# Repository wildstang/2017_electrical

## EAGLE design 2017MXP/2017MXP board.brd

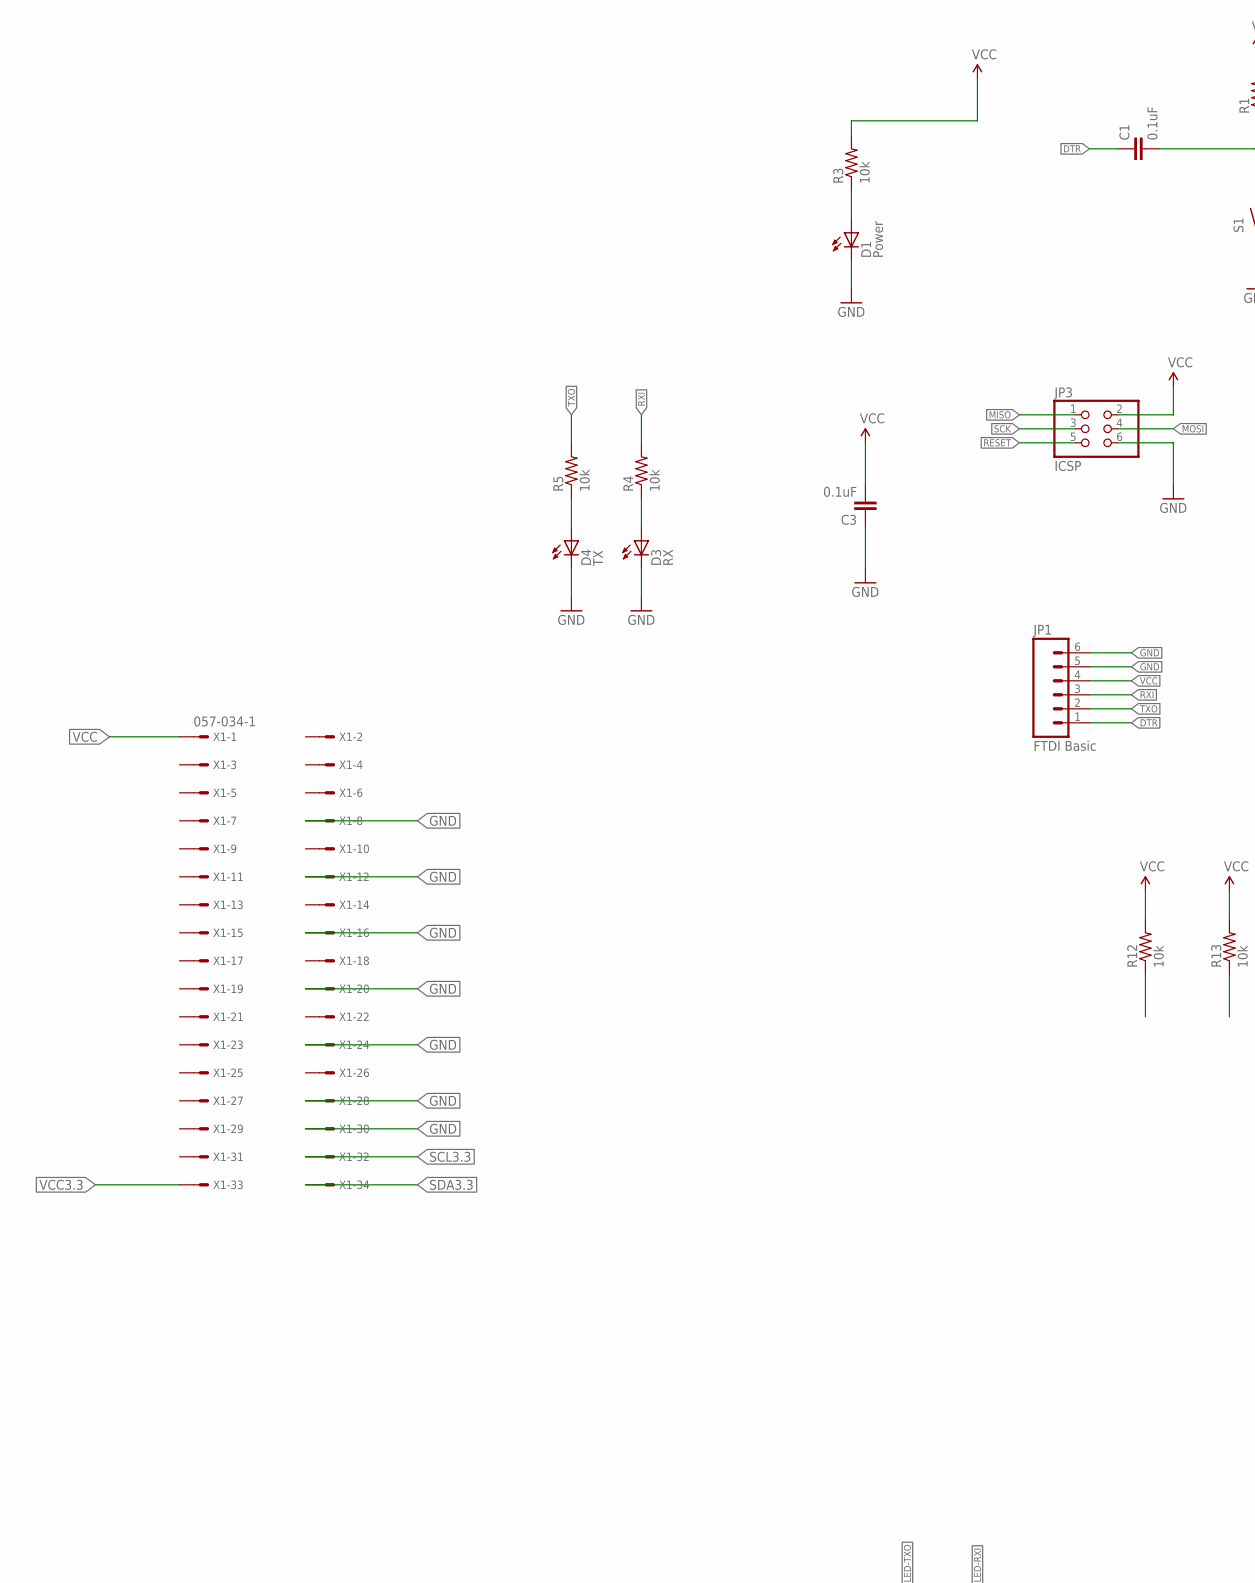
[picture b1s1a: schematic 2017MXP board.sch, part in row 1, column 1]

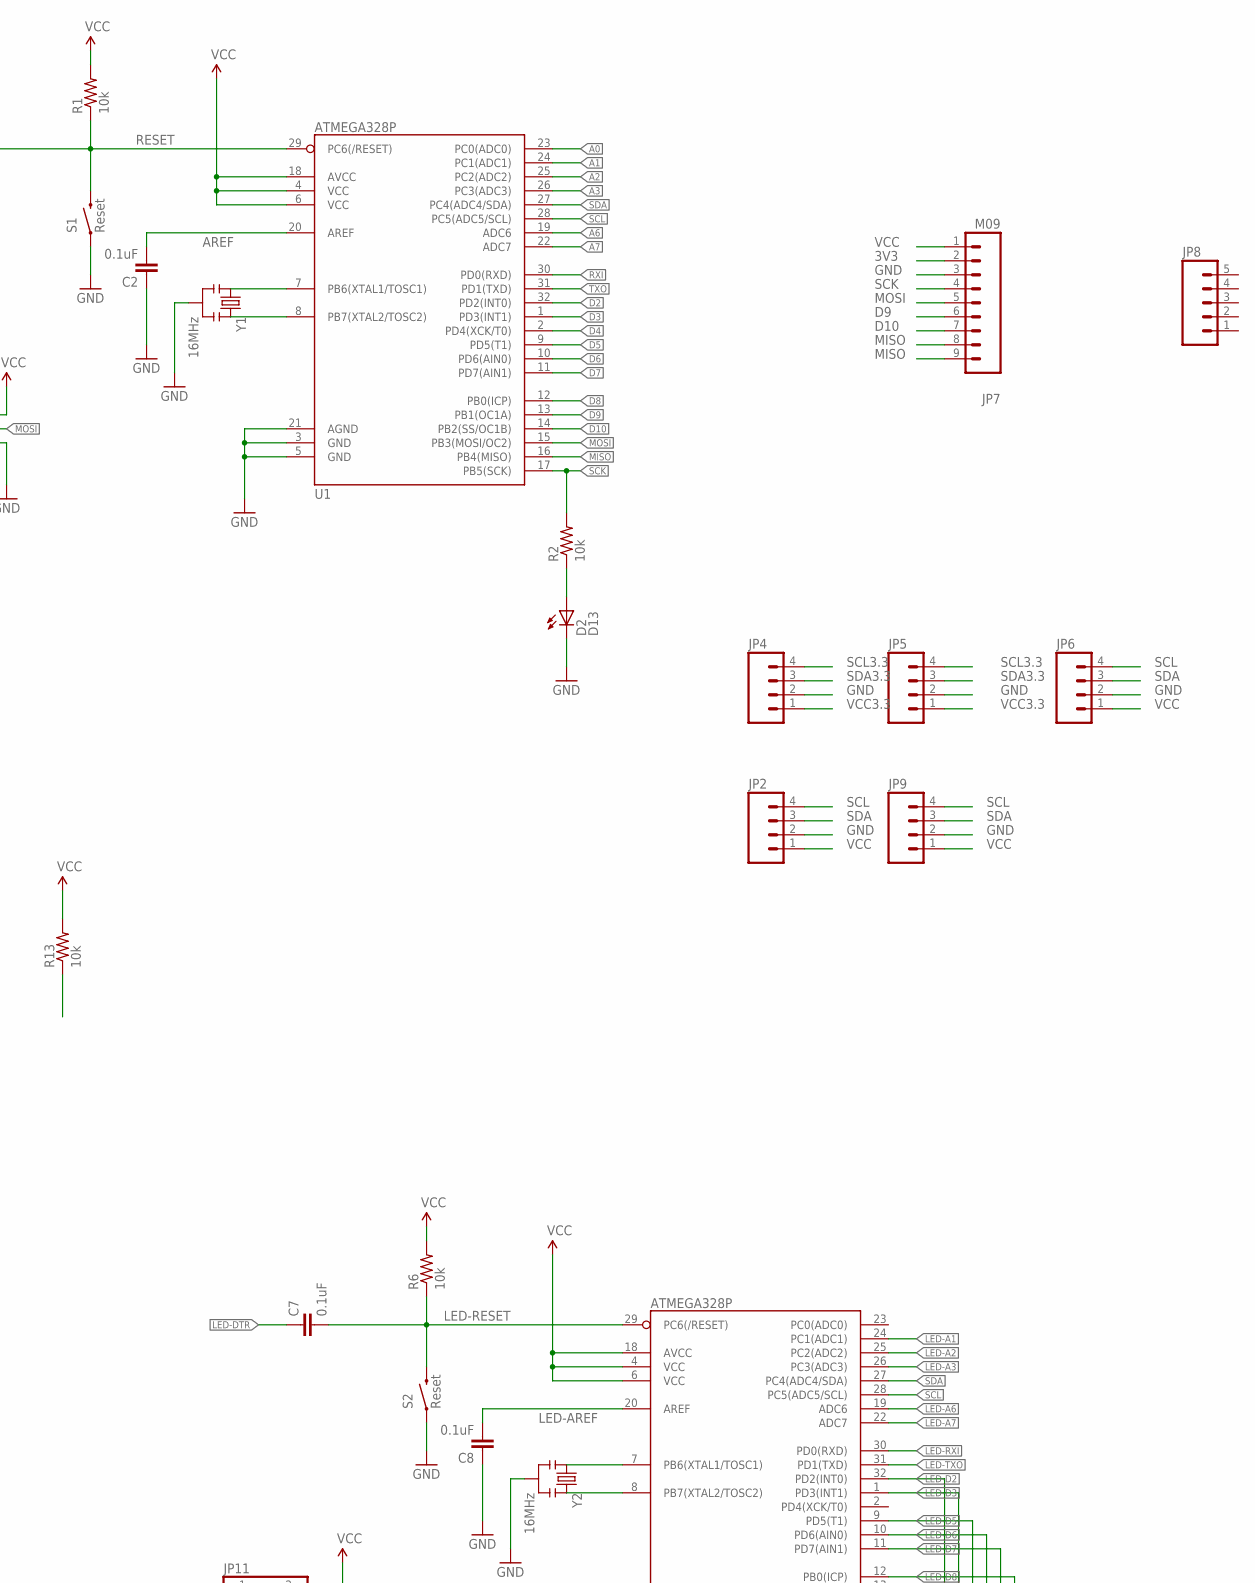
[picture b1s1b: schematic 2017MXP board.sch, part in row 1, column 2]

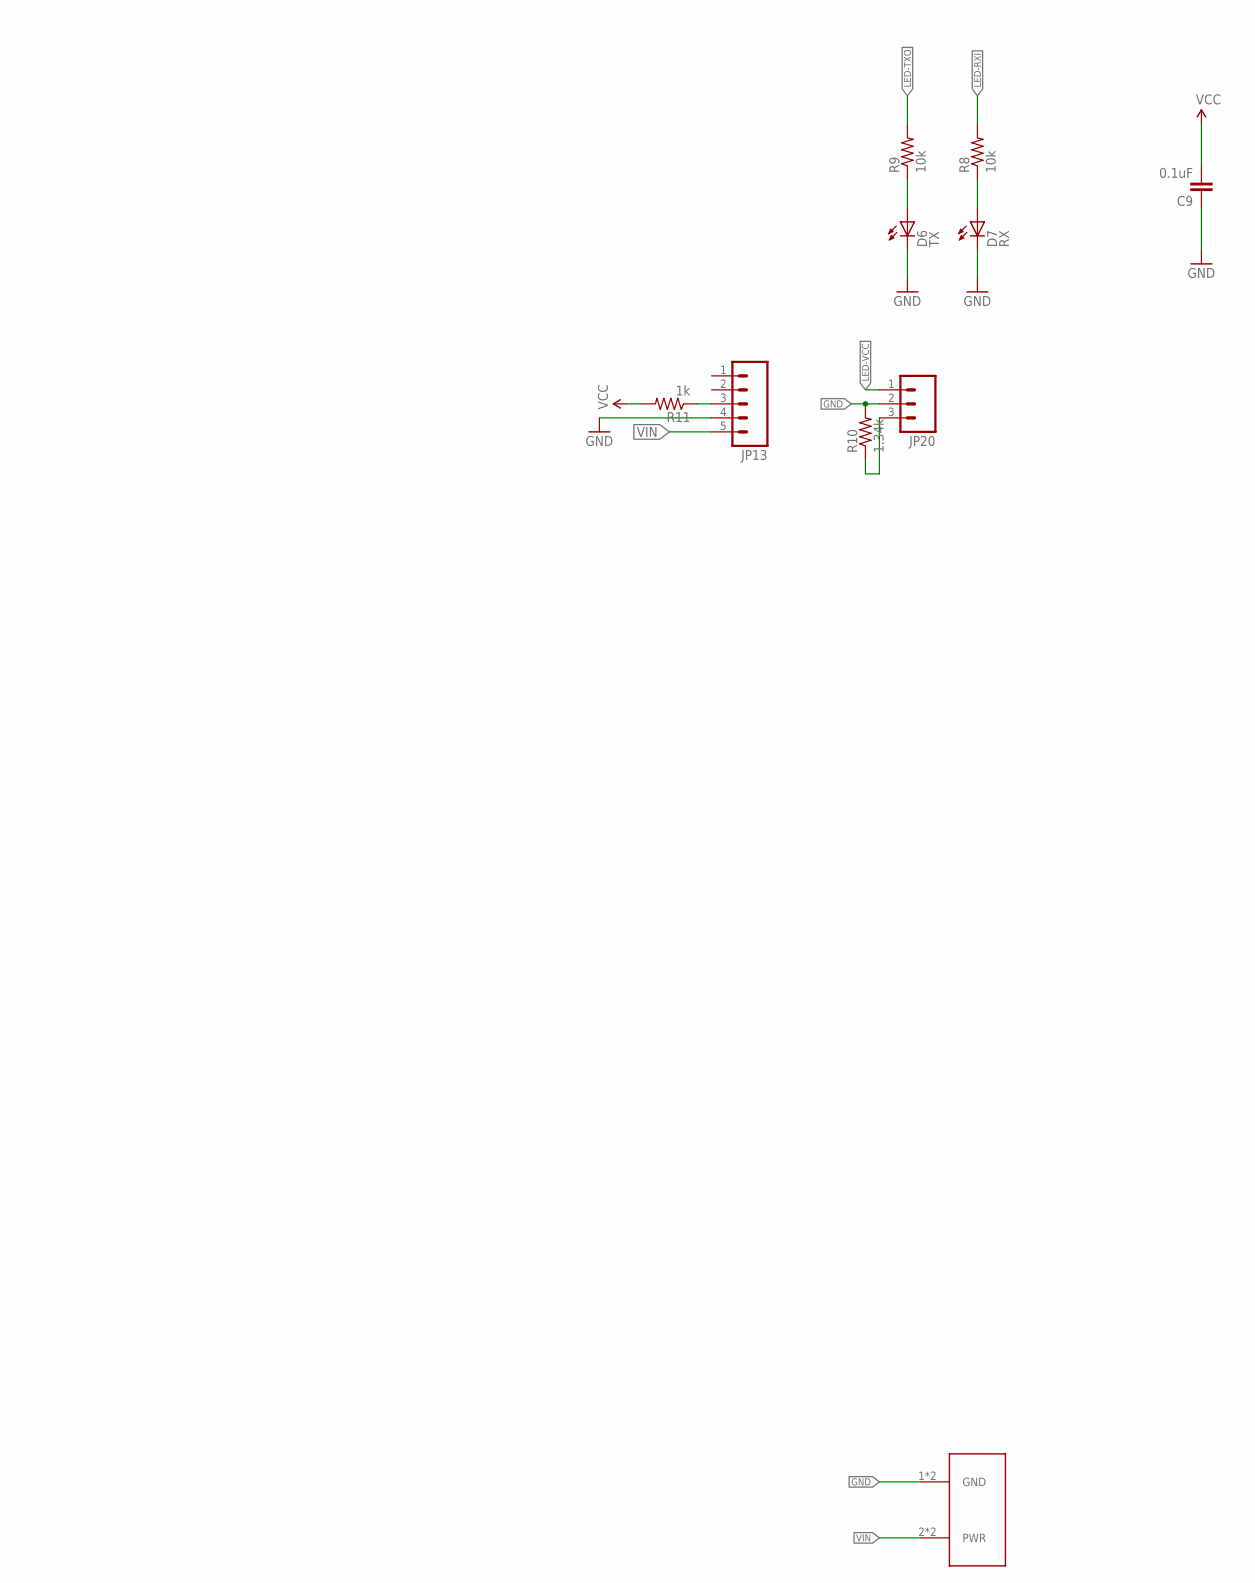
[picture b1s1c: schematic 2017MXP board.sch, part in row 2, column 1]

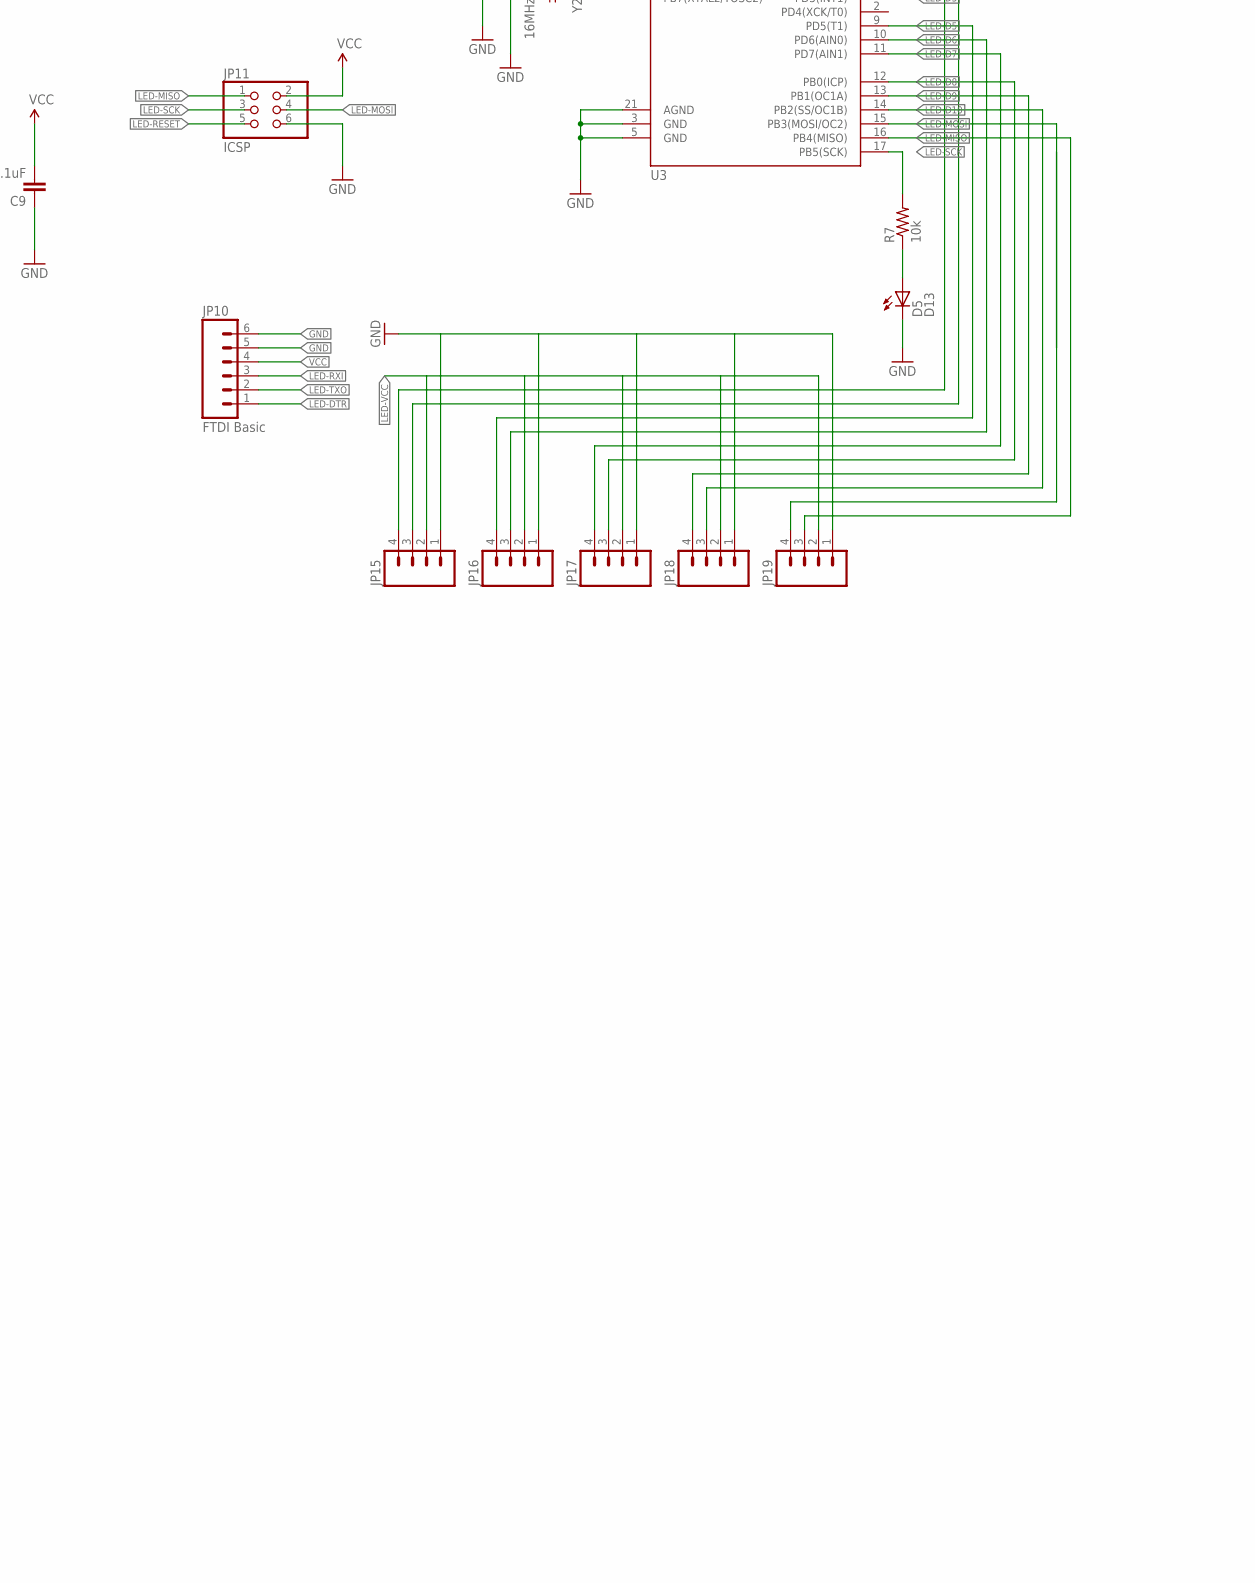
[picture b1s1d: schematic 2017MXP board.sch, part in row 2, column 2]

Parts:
C1, C2, C3, C7, C8, C9: 0.1uF; 0603-CAP
D1: Power; LED-0603
D2, D5: D13; LED-0603
D3, D7: RX; LED-0603
D4, D6: TX; LED-0603
JP1, JP10: FTDI Basic; 1X06
JP2, JP4, JP5, JP6, JP9, JP15, JP16, JP17, JP18, JP19: M04PTH; 1X04
JP3, JP11: ICSP; 2X03
JP7: M09; 1X09
JP8, JP13: M05PTH; 1X05
JP20: M03PTH; 1X03
R1, R2, R3, R4, R5, R6, R7, R8, R9, R12, R13: 10k; 0603-RES
R10: 1.34k; AXIAL-0.3
R11: 1k; AXIAL-0.3
S1, S2: Reset; TACTILE_SWITCH_SMD
U1, U3: ATMEGA328P; TQFP32-08
U$2: LSF-SMT
X1: 057-034-1
Y1, Y2: 16MHz; RESONATOR-SMD

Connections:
3V3: JP7.2
A0: U1.23 (PC0(ADC0))
A1: U1.24 (PC1(ADC1))
A2: U1.25 (PC2(ADC2))
A3: U1.26 (PC3(ADC3))
A6: U1.19 (ADC6)
A7: U1.22 (ADC7)
AREF: C2.2, U1.20 (AREF)
D2: U1.32 (PD2(INT0))
D3: U1.1 (PD3(INT1))
D4: U1.2 (PD4(XCK/T0))
D5: U1.9 (PD5(T1))
D6: U1.10 (PD6(AIN0))
D7: U1.11 (PD7(AIN1))
D8: U1.12 (PB0(ICP))
D9: JP7.6, U1.13 (PB1(OC1A))
D10: JP7.7, U1.14 (PB2(SS/OC1B))
DTR: C1.1, JP1.1
GND: C2.1, C3.1, C8.1, C9.1, D1.C, D2.C, D3.C, D4.C, D5.C, D6.C, D7.C, JP1.5, JP1.6, JP2.2, JP3.6, JP4.2, JP5.2, JP6.2, JP7.3, JP9.2, JP10.5, JP10.6, JP11.6, JP13.4, JP15.1, JP16.1, JP17.1, JP18.1, JP19.1, JP20.2, R10.P$2 (2), S1.1, S2.1, U1.3 (GND), U1.5 (GND), U1.21 (AGND), U3.3 (GND), U3.5 (GND), U3.21 (AGND), U$2.1 (GND), U$2.1-2 (GND), X1.8, X1.12, X1.16, X1.20, X1.24, X1.28, X1.30, Y1.2, Y2.2
LED-A1: U3.24 (PC1(ADC1))
LED-A2: U3.25 (PC2(ADC2))
LED-A3: U3.26 (PC3(ADC3))
LED-A6: U3.19 (ADC6)
LED-A7: U3.22 (ADC7)
LED-AREF: C8.2, U3.20 (AREF)
LED-D2: JP15.4, U3.32 (PD2(INT0))
LED-D3: JP15.3, U3.1 (PD3(INT1))
LED-D5: JP16.4, U3.9 (PD5(T1))
LED-D6: JP16.3, U3.10 (PD6(AIN0))
LED-D7: JP17.4, U3.11 (PD7(AIN1))
LED-D8: JP17.3, U3.12 (PB0(ICP))
LED-D9: JP18.4, U3.13 (PB1(OC1A))
LED-D10: JP18.3, U3.14 (PB2(SS/OC1B))
LED-DTR: C7.1, JP10.1
LED-MISO: JP11.1, JP19.3, U3.16 (PB4(MISO))
LED-MOSI: JP11.4, JP19.4, U3.15 (PB3(MOSI/OC2))
LED-RESET: C7.2, JP11.5, R6.1, S2.3 (2), U3.29 (PC6(/RESET))
LED-RXI: JP10.3, R8.2, U3.30 (PD0(RXD))
LED-SCK: JP11.3, R7.2, U3.17 (PB5(SCK))
LED-TXO: JP10.2, R9.2, U3.31 (PD1(TXD))
LED-VCC: JP15.2, JP16.2, JP17.2, JP18.2, JP19.2, JP20.1
MISO: JP3.1, JP7.8, JP7.9, U1.16 (PB4(MISO))
MOSI: JP3.4, JP7.5, U1.15 (PB3(MOSI/OC2))
unnamed: U1.7 (PB6(XTAL1/TOSC1)), Y1.1
unnamed: U1.8 (PB7(XTAL2/TOSC2)), Y1.3
unnamed: D1.A, R3.1
unnamed: D2.A, R2.1
unnamed: D3.A, R4.1
unnamed: D4.A, R5.1
unnamed: U3.7 (PB6(XTAL1/TOSC1)), Y2.1
unnamed: U3.8 (PB7(XTAL2/TOSC2)), Y2.3
unnamed: D5.A, R7.1
unnamed: D6.A, R9.1
unnamed: D7.A, R8.1
unnamed: JP20.3, R10.P$1 (1)
unnamed: JP13.3, R11.P$1 (1)
RESET: C1.2, JP3.5, R1.1, S1.3 (2), U1.29 (PC6(/RESET))
RXI: JP1.3, R4.2, U1.30 (PD0(RXD))
SCK: JP3.3, JP7.4, R2.2, U1.17 (PB5(SCK))
SCL: JP2.4, JP6.4, JP9.4, R13.1, U1.28 (PC5(ADC5/SCL)), U3.28 (PC5(ADC5/SCL))
SCL3.3: JP4.4, JP5.4, X1.32
SDA: JP2.3, JP6.3, JP9.3, R12.1, U1.27 (PC4(ADC4/SDA)), U3.27 (PC4(ADC4/SDA))
SDA3.3: JP4.3, JP5.3, X1.34
TXO: JP1.2, R5.2, U1.31 (PD1(TXD))
VCC: C3.2, C9.2, JP1.4, JP2.1, JP3.2, JP6.1, JP7.1, JP9.1, JP10.4, JP11.2, R1.2, R3.2, R6.2, R11.P$2 (2), R12.2, R13.2, U1.4 (VCC), U1.6 (VCC), U1.18 (AVCC), U3.4 (VCC), U3.6 (VCC), U3.18 (AVCC), X1.1
VCC3.3: JP4.1, JP5.1, X1.33
VIN: JP13.5, U$2.2 (PWR), U$2.2-2 (PWR)

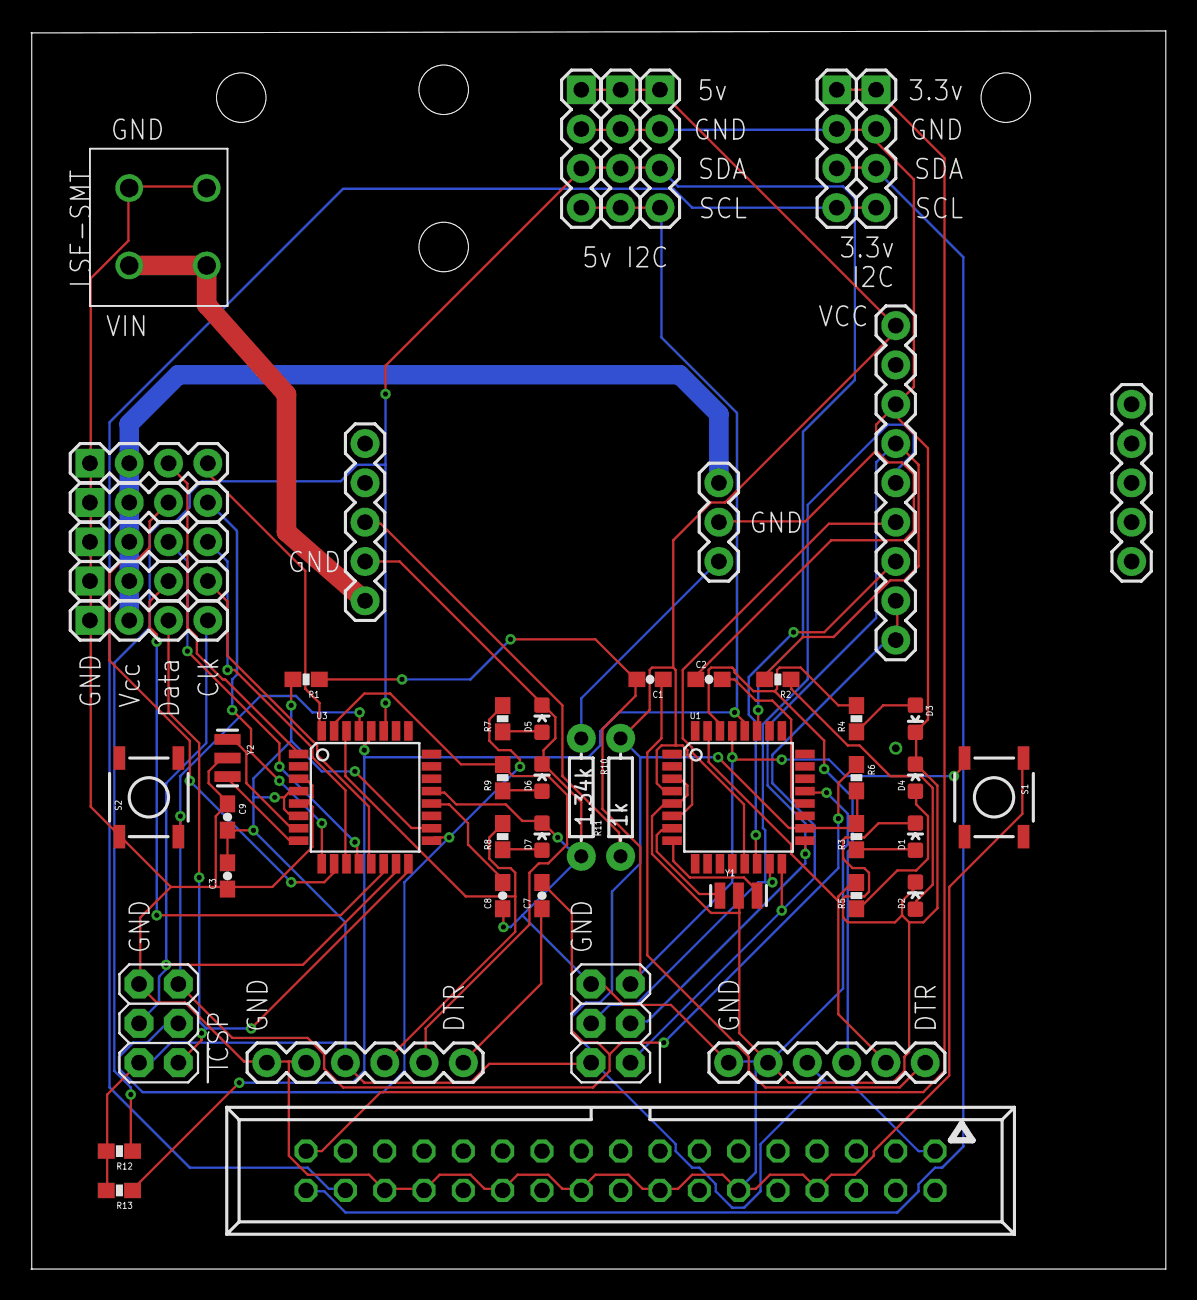
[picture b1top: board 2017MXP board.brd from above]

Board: 2 copper layers, 73.3 x 80.0 mm, 52 parts (0 on the bottom side), 48 nets.

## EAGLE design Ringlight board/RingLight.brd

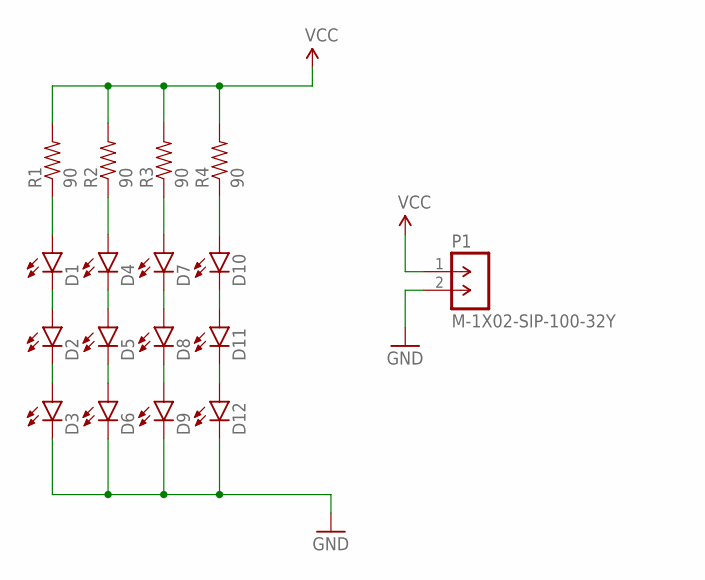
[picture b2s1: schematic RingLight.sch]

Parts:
D1, D2, D3, D4, D5, D6, D7, D8, D9, D10, D11, D12: LED1206; LED-1206
P1: M-1X02-SIP-100-32Y; SIP-100-02-32Y
R1, R2, R3, R4: 90; 1206

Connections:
GND: D3.C, D6.C, D9.C, D12.C, P1.2
unnamed: D1.A, R1.1
unnamed: D4.A, R2.1
unnamed: D7.A, R3.1
unnamed: D10.A, R4.1
unnamed: D1.C, D2.A
unnamed: D4.C, D5.A
unnamed: D7.C, D8.A
unnamed: D10.C, D11.A
unnamed: D11.C, D12.A
unnamed: D8.C, D9.A
unnamed: D5.C, D6.A
unnamed: D2.C, D3.A
VCC: P1.1, R1.2, R2.2, R3.2, R4.2

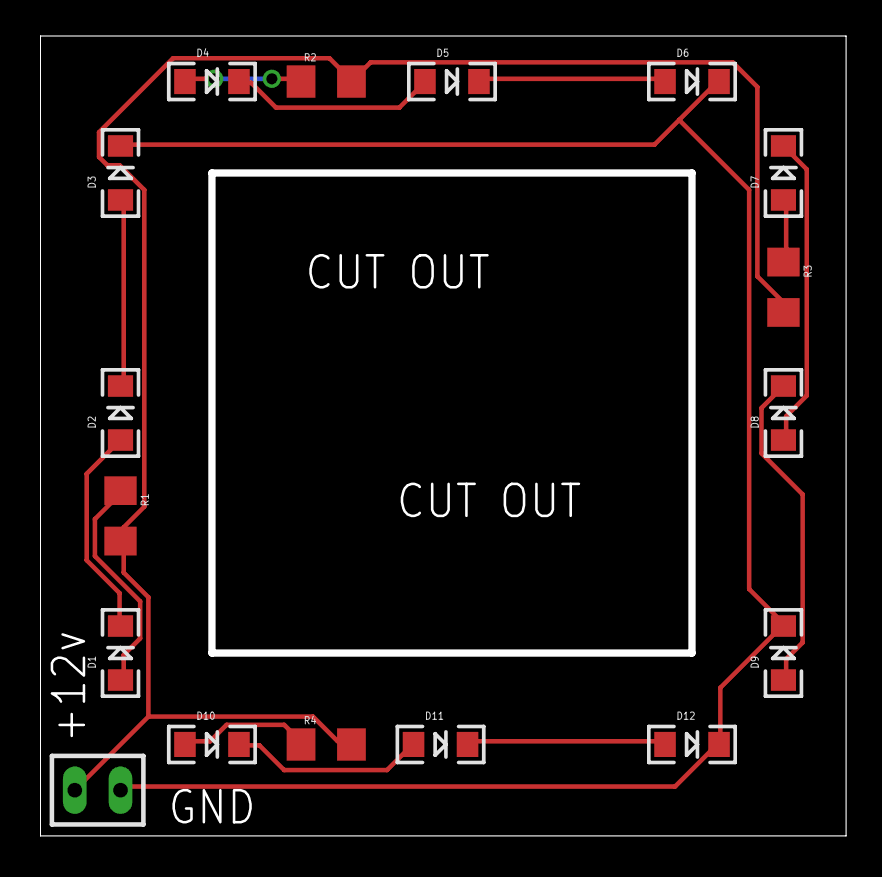
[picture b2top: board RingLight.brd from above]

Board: 2 copper layers, 44.8 x 44.4 mm, 17 parts (0 on the bottom side), 14 nets.

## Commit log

2017-01-15 Added 2015 board
2017-01-15 Created branch and added Talon Breakout boards
2017-01-21 Added 2017 MXP
2017-02-02 Added Ring light sketch and board
2017-02-04 Updated the boards for final layout.
2017-03-22 Added updated ringlight board in Ringlight2.0
2017-03-22 Pushed routed board, realized version from yesterday hadn't been routed
2021-08-29 Combined 2017 electrical repos

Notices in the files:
parts and their libraries:
SparkFun-Connectors: Licensing: Creative Commons ShareAlike 4.0 International - https://creativecommons.org/licenses/by-sa/4.0
con-headers-jp: Copyright (C) 2008, Bob Starr
